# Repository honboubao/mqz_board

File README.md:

# Micro Quertz Keyboard PCB

KiCad 7 PCB layout project for a 32 key keyboard with Kailh PG1232 Mini Choc switches and a nice!nano microcontroller.

[Firmware](https://github.com/honboubao/mqz_fw)

[Keyboard layout](http://www.keyboard-layout-editor.com/#/gists/12281aabe024b50dbcfd42017a9aa722)

## Dependencies

KiCad symbols and footprints. Place next to this project folder.

[Choc PG1232 switches by @crides](https://github.com/crides/choc)

[nice!nano BLE microcontroller by @bstiq](https://github.com/bstiq/nice-nano-kicad)

# License

This work is licensed under the GNU GPLv3.

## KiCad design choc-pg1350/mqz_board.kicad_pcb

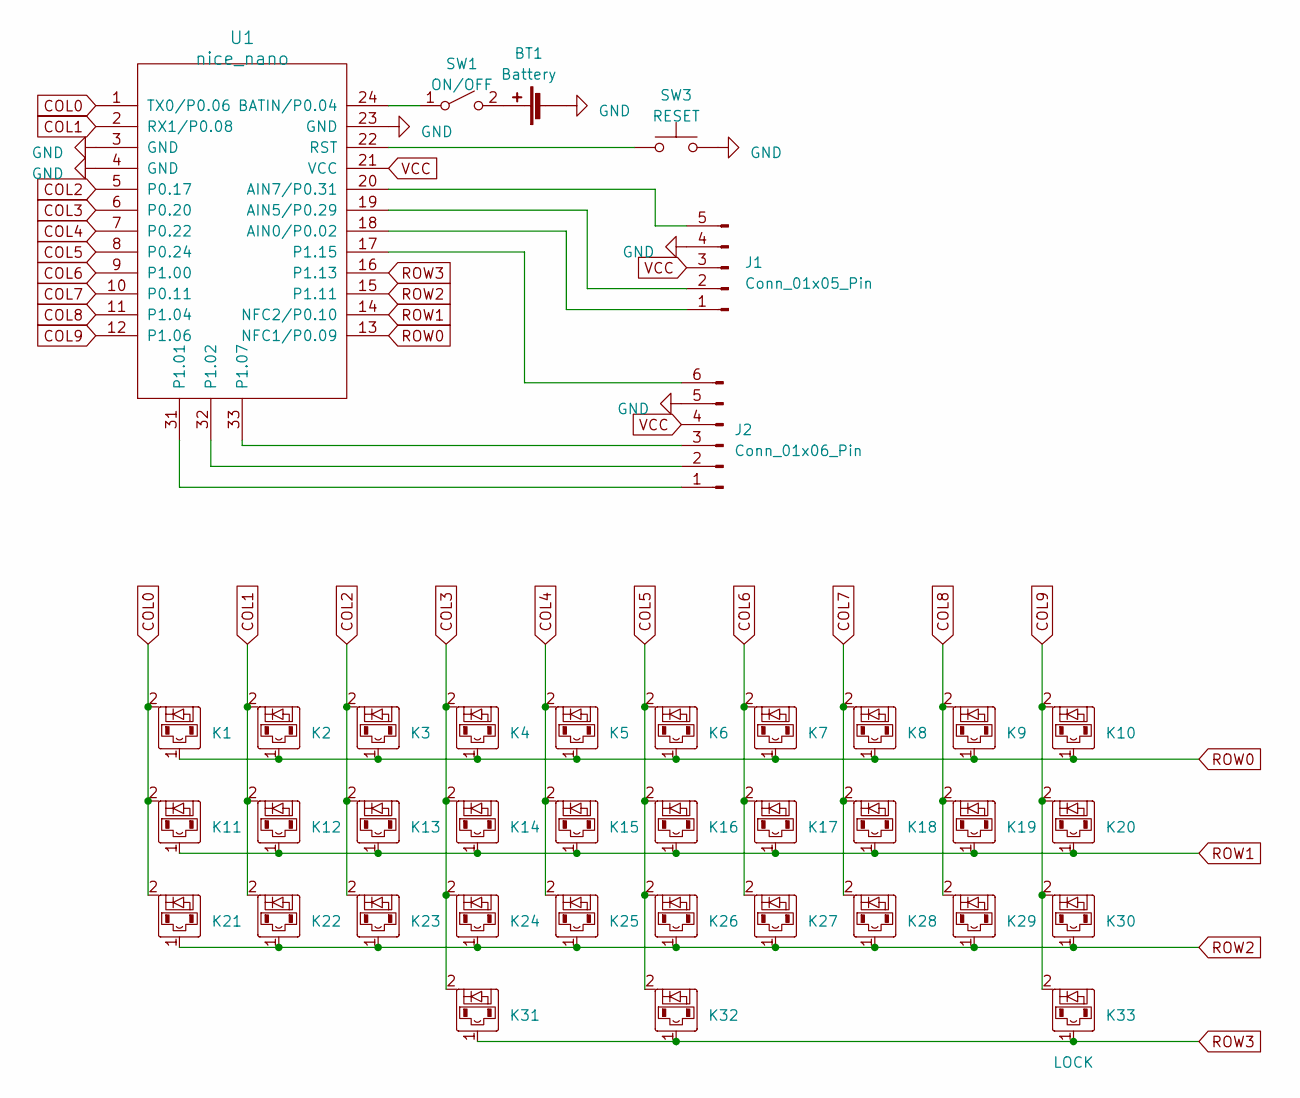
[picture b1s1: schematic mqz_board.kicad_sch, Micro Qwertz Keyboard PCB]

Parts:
BT1: Battery; SolderWire-0.75sqmm_1x02_P7mm_D1.25mm_OD3.5mm
J1: Conn_01x05_Pin; PinSocket_1x05_P2.54mm_Vertical
J2: Conn_01x06_Pin; PinSocket_1x06_P2.54mm_Vertical
K1, K2, K3, K4, K5, K6, K7, K8, K9, K10, K11, K12, K13, K14, K15, K16, K17, K18, K19, K20, K21, K22, K23, K24, K25, K26, K27, K28, K29, K30, K31, K32: diode-choc; pg1232-D
K33: LOCK; pg1350-D
SW1: ON/OFF; SW_CuK_OS102011MA1QN1_SPDT_Angled
SW3: RESET; SW_PUSH_6mm_H5mm
U1: nice_nano

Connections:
COL0: K1.2, K11.2, K21.2, U1.1 (TX0/P0.06)
COL1: K2.2, K12.2, K22.2, U1.2 (RX1/P0.08)
COL2: K3.2, K13.2, K23.2, U1.5 (P0.17)
COL3: K4.2, K14.2, K24.2, K31.2, U1.6 (P0.20)
COL4: K5.2, K15.2, K25.2, U1.7 (P0.22)
COL5: K6.2, K16.2, K26.2, K32.2, U1.8 (P0.24)
COL6: K7.2, K17.2, K27.2, U1.9 (P1.00)
COL7: K8.2, K18.2, K28.2, U1.10 (P0.11)
COL8: K9.2, K19.2, K29.2, U1.11 (P1.04)
COL9: K10.2, K20.2, K30.2, K33.2, U1.12 (P1.06)
GND: BT1.2 (-), J1.4, J2.5, SW3.2, U1.3 (GND), U1.4 (GND), U1.23 (GND)
unnamed: BT1.1 (+), SW1.2 (B)
unnamed: J1.1, U1.18 (AIN0/P0.02)
unnamed: J1.2, U1.19 (AIN5/P0.29)
unnamed: J1.5, U1.20 (AIN7/P0.31)
unnamed: J2.1, U1.31 (P1.01)
unnamed: J2.2, U1.32 (P1.02)
unnamed: J2.3, U1.33 (P1.07)
unnamed: J2.6, U1.17 (P1.15)
unnamed: SW1.1 (A), U1.24 (BATIN/P0.04)
unnamed: SW3.1, U1.22 (RST)
ROW0: K1.1, K2.1, K3.1, K4.1, K5.1, K6.1, K7.1, K8.1, K9.1, K10.1, U1.13 (NFC1/P0.09)
ROW1: K11.1, K12.1, K13.1, K14.1, K15.1, K16.1, K17.1, K18.1, K19.1, K20.1, U1.14 (NFC2/P0.10)
ROW2: K21.1, K22.1, K23.1, K24.1, K25.1, K26.1, K27.1, K28.1, K29.1, K30.1, U1.15 (P1.11)
ROW3: K31.1, K32.1, K33.1, U1.16 (P1.13)
VCC: J1.3, J2.4, U1.21 (VCC)

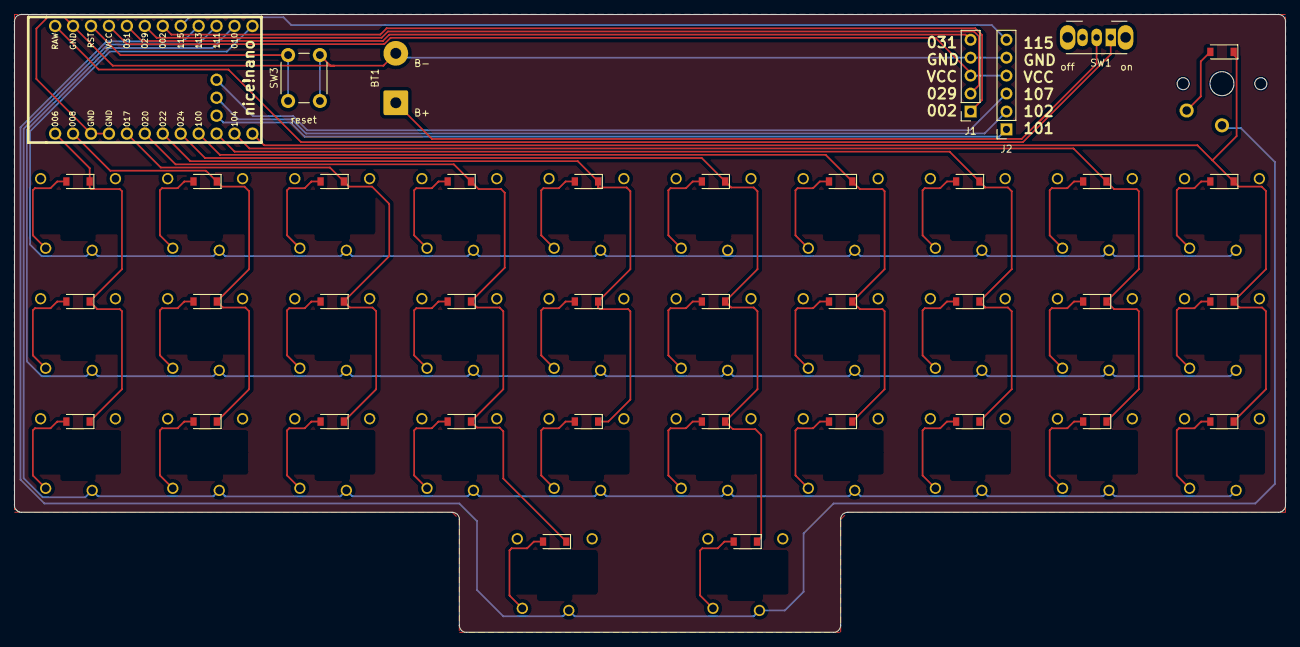
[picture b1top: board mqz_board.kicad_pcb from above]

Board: 2 copper layers, 180.0 x 87.5 mm, 39 parts (0 on the bottom side), 26 nets.

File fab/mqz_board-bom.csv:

Comment,Designator,Footprint,JLCPCB_Part_#
Kathode_towards_right_pad_(closed_end_of_rectangle_on_silkscreen),K1,pg1232-D,C81598
Kathode_towards_right_pad_(closed_end_of_rectangle_on_silkscreen),K2,pg1232-D,C81598
Kathode_towards_right_pad_(closed_end_of_rectangle_on_silkscreen),K3,pg1232-D,C81598
Kathode_towards_right_pad_(closed_end_of_rectangle_on_silkscreen),K4,pg1232-D,C81598
Kathode_towards_right_pad_(closed_end_of_rectangle_on_silkscreen),K5,pg1232-D,C81598
Kathode_towards_right_pad_(closed_end_of_rectangle_on_silkscreen),K6,pg1232-D,C81598
Kathode_towards_right_pad_(closed_end_of_rectangle_on_silkscreen),K7,pg1232-D,C81598
Kathode_towards_right_pad_(closed_end_of_rectangle_on_silkscreen),K8,pg1232-D,C81598
Kathode_towards_right_pad_(closed_end_of_rectangle_on_silkscreen),K9,pg1232-D,C81598
Kathode_towards_right_pad_(closed_end_of_rectangle_on_silkscreen),K10,pg1232-D,C81598
Kathode_towards_right_pad_(closed_end_of_rectangle_on_silkscreen),K11,pg1232-D,C81598
Kathode_towards_right_pad_(closed_end_of_rectangle_on_silkscreen),K12,pg1232-D,C81598
Kathode_towards_right_pad_(closed_end_of_rectangle_on_silkscreen),K13,pg1232-D,C81598
Kathode_towards_right_pad_(closed_end_of_rectangle_on_silkscreen),K14,pg1232-D,C81598
Kathode_towards_right_pad_(closed_end_of_rectangle_on_silkscreen),K15,pg1232-D,C81598
Kathode_towards_right_pad_(closed_end_of_rectangle_on_silkscreen),K16,pg1232-D,C81598
Kathode_towards_right_pad_(closed_end_of_rectangle_on_silkscreen),K17,pg1232-D,C81598
Kathode_towards_right_pad_(closed_end_of_rectangle_on_silkscreen),K18,pg1232-D,C81598
Kathode_towards_right_pad_(closed_end_of_rectangle_on_silkscreen),K19,pg1232-D,C81598
Kathode_towards_right_pad_(closed_end_of_rectangle_on_silkscreen),K20,pg1232-D,C81598
Kathode_towards_right_pad_(closed_end_of_rectangle_on_silkscreen),K21,pg1232-D,C81598
Kathode_towards_right_pad_(closed_end_of_rectangle_on_silkscreen),K22,pg1232-D,C81598
Kathode_towards_right_pad_(closed_end_of_rectangle_on_silkscreen),K23,pg1232-D,C81598
Kathode_towards_right_pad_(closed_end_of_rectangle_on_silkscreen),K24,pg1232-D,C81598
Kathode_towards_right_pad_(closed_end_of_rectangle_on_silkscreen),K25,pg1232-D,C81598
Kathode_towards_right_pad_(closed_end_of_rectangle_on_silkscreen),K26,pg1232-D,C81598
Kathode_towards_right_pad_(closed_end_of_rectangle_on_silkscreen),K27,pg1232-D,C81598
Kathode_towards_right_pad_(closed_end_of_rectangle_on_silkscreen),K28,pg1232-D,C81598
Kathode_towards_right_pad_(closed_end_of_rectangle_on_silkscreen),K29,pg1232-D,C81598
Kathode_towards_right_pad_(closed_end_of_rectangle_on_silkscreen),K30,pg1232-D,C81598
Kathode_towards_right_pad_(closed_end_of_rectangle_on_silkscreen),K31,pg1232-D,C81598
Kathode_towards_right_pad_(closed_end_of_rectangle_on_silkscreen),K32,pg1232-D,C81598
Kathode_towards_right_pad_(closed_end_of_rectangle_on_silkscreen),K33,pg1350-D,C81598

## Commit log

2023-09-28 move project files to subfolder
2023-09-28 copy project for pg 1350 choc switch footprint
2023-09-28 update footprint library paths
